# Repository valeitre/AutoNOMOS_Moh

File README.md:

# AutoNOMOS_Moh
Avances sobre el vehículo autónomo, paquetes ros, simuladores, etc.

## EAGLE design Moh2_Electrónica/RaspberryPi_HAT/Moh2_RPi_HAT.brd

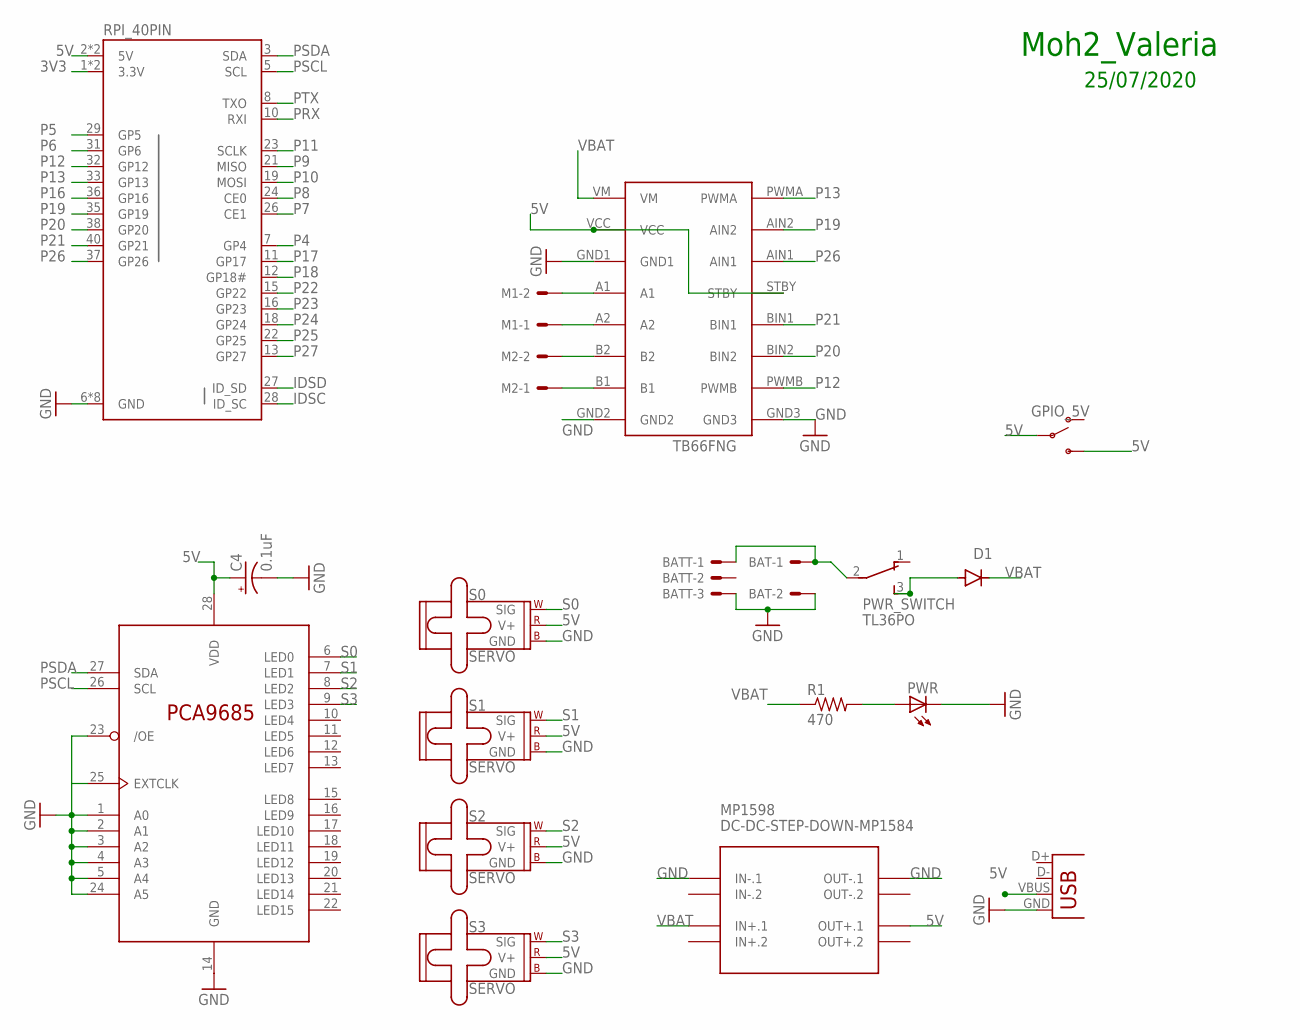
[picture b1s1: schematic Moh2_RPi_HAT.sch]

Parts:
BAT: 22-05-7028-02; 7395-02
BATT: 22-05-7038-03; 7395-03
C4: 0.1uF; E1,8-4
D1: 1N5400; DO201-15
GPIO_5V: SWITCH-SPDT-PTH-11.6X4.0MM; SWITCH_SPDT_PTH_11.6X4.0MM
M1, M2: 22-05-7028-02; 7395-02
MP1598: DC-DC-STEP-DOWN-MP1584
PCA96: PCA9685PW; TSSOP28
PWR: LED5MM
PWR_SWITCH: TL36PO; TL3XPO
R1: 470; 0204/7
RPI_40PIN: RASPBERRYPI-40-PIN-GPIO_PTH_NO_SHROUD; 2X20
RPI_PWR: USB-A-H
S0, S1, S2, S3: SERVO; 1X03
TB66FNG: TB6612FNG

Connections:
3V3: RPI_40PIN.1 (3.3V), RPI_40PIN.17 (3.3V)
5V: C4.+, GPIO_5V.2, GPIO_5V.3 (S), MP1598.OUT+.1, PCA96.28 (VDD), RPI_40PIN.2 (5V), RPI_40PIN.4 (5V), RPI_PWR.VBUS, S0.2 (V+), S1.2 (V+), S2.2 (V+), S3.2 (V+), TB66FNG.STBY, TB66FNG.VCC
11.1V+: BAT.1, BATT.1, PWR_SWITCH.2
GND: BAT.2, BATT.3, C4.-, MP1598.IN-.1, MP1598.OUT-.1, PCA96.1 (A0), PCA96.2 (A1), PCA96.3 (A2), PCA96.4 (A3), PCA96.5 (A4), PCA96.14 (GND), PCA96.23 (/OE), PCA96.24 (A5), PCA96.25 (EXTCLK), PWR.K (C), RPI_40PIN.6 (GND), RPI_40PIN.9 (GND), RPI_40PIN.14 (GND), RPI_40PIN.20 (GND), RPI_40PIN.25 (GND), RPI_40PIN.30 (GND), RPI_40PIN.34 (GND), RPI_40PIN.39 (GND), RPI_PWR.GND, S0.3 (GND), S1.3 (GND), S2.3 (GND), S3.3 (GND), TB66FNG.GND1, TB66FNG.GND2, TB66FNG.GND3
IDSC: RPI_40PIN.28 (ID_SC)
IDSD: RPI_40PIN.27 (ID_SD)
unnamed: M2.2, TB66FNG.B2
unnamed: D1.A, PWR_SWITCH.3 (S)
unnamed: M1.2, TB66FNG.A1
unnamed: M1.1, TB66FNG.A2
unnamed: M2.1, TB66FNG.B1
unnamed: PWR.A, R1.2
P4: RPI_40PIN.7 (GP4)
P5: RPI_40PIN.29 (GP5)
P6: RPI_40PIN.31 (GP6)
P7: RPI_40PIN.26 (CE1)
P8: RPI_40PIN.24 (CE0)
P9: RPI_40PIN.21 (MISO)
P10: RPI_40PIN.19 (MOSI)
P11: RPI_40PIN.23 (SCLK)
P12: RPI_40PIN.32 (GP12), TB66FNG.PWMB
P13: RPI_40PIN.33 (GP13), TB66FNG.PWMA
P16: RPI_40PIN.36 (GP16)
P17: RPI_40PIN.11 (GP17)
P18: RPI_40PIN.12 (GP18#)
P19: RPI_40PIN.35 (GP19), TB66FNG.AIN2
P20: RPI_40PIN.38 (GP20), TB66FNG.BIN2
P21: RPI_40PIN.40 (GP21), TB66FNG.BIN1
P22: RPI_40PIN.15 (GP22)
P23: RPI_40PIN.16 (GP23)
P24: RPI_40PIN.18 (GP24)
P25: RPI_40PIN.22 (GP25)
P26: RPI_40PIN.37 (GP26), TB66FNG.AIN1
P27: RPI_40PIN.13 (GP27)
PRX: RPI_40PIN.10 (RXI)
PSCL: PCA96.26 (SCL), RPI_40PIN.5 (SCL)
PSDA: PCA96.27 (SDA), RPI_40PIN.3 (SDA)
PTX: RPI_40PIN.8 (TXO)
S0: PCA96.6 (LED0), S0.1 (SIG)
S1: PCA96.7 (LED1), S1.1 (SIG)
S2: PCA96.8 (LED2), S2.1 (SIG)
S3: PCA96.9 (LED3), S3.1 (SIG)
VBAT: D1.C, MP1598.IN+.1, R1.1, TB66FNG.VM

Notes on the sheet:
Moh2_Valeria
25/07/2020

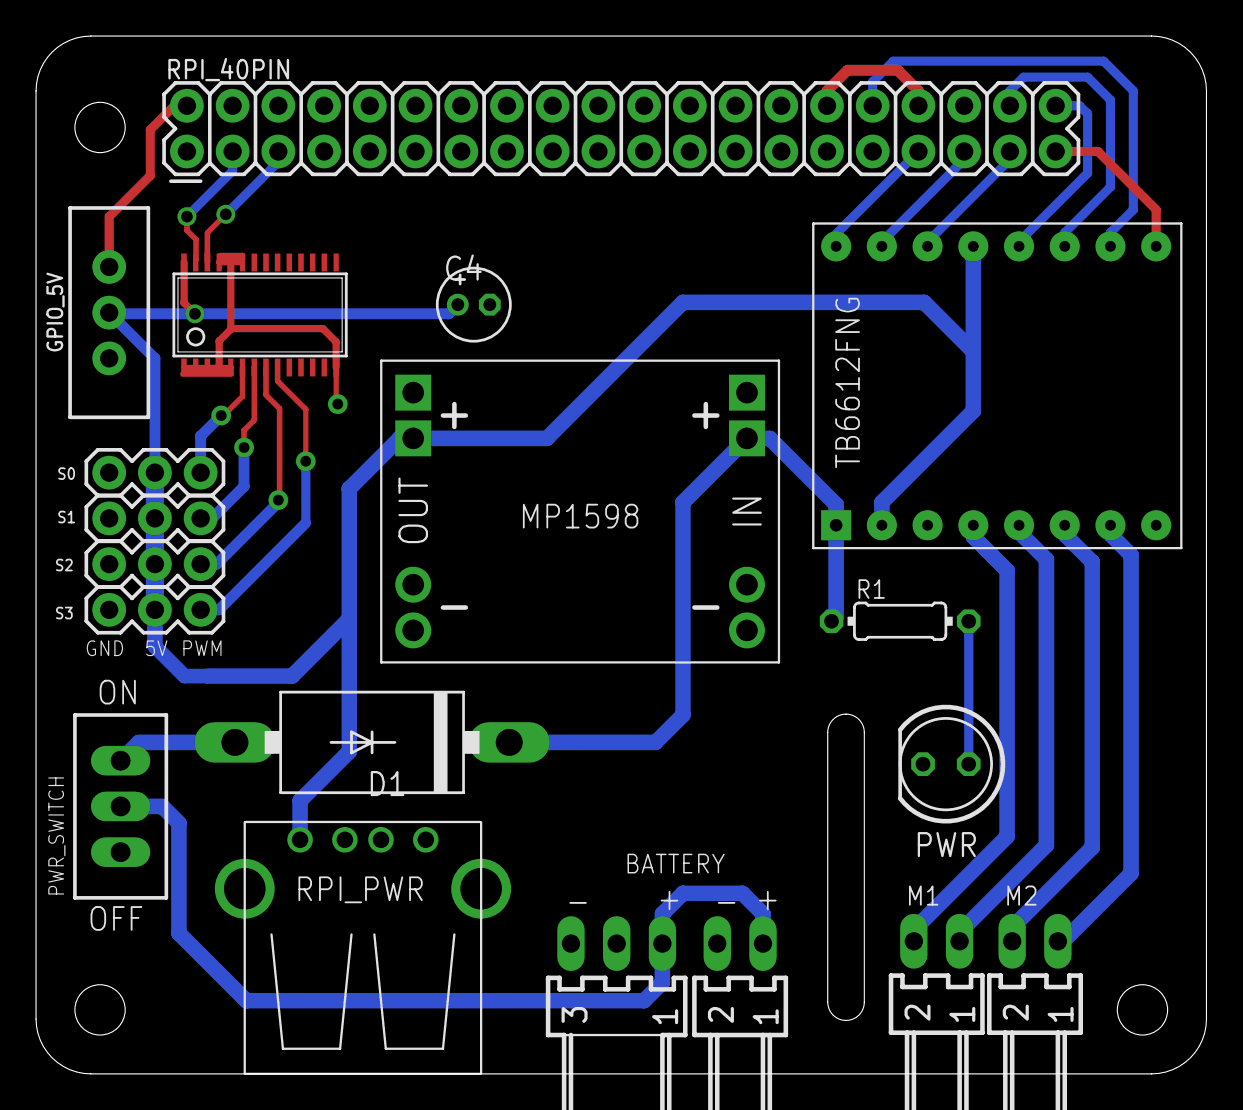
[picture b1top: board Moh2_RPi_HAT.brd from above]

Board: 2 copper layers, 65.0 x 57.7 mm, 19 parts (0 on the bottom side), 23 nets.

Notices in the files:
parts and their libraries:
SparkFun-Connectors: Licensing: Creative Commons ShareAlike 4.0 International - https://creativecommons.org/licenses/by-sa/4.0
diy-modules: Released under the Creative Commons Attribution 4.0 International License: http://creativecommons.org/licenses/by/4.0
